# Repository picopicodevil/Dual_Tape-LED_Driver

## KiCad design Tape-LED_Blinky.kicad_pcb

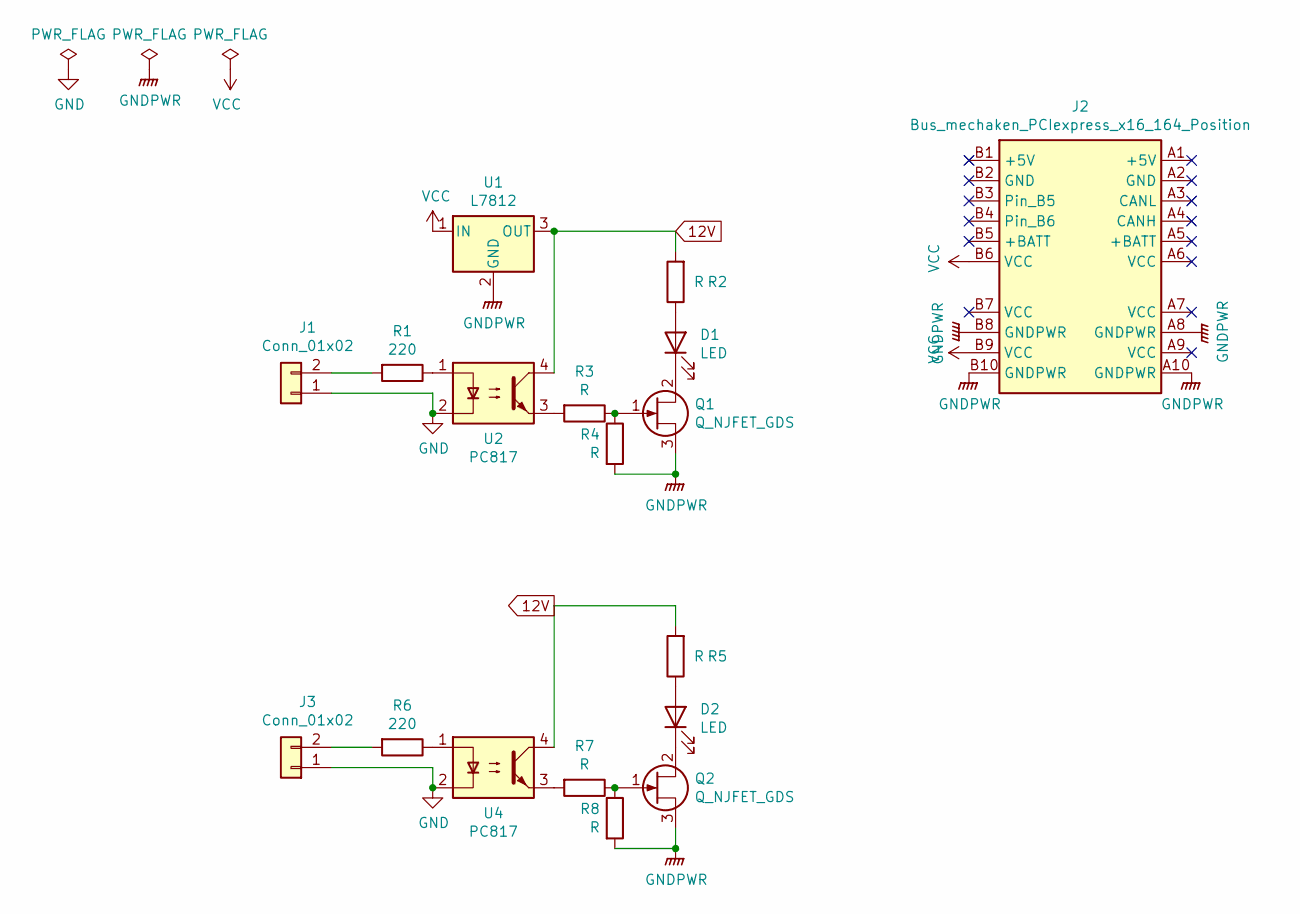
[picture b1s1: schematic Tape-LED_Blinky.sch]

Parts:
D1, D2: LED; PinHeader_1x02_P2.54mm_Vertical
J1, J3: Conn_01x02; PinHeader_1x02_P2.54mm_Vertical
J2: Bus_mechaken_PCIexpress_x16_164_Position; BUS_mechaken_PCIexpress_x16
Q1, Q2: Q_NJFET_GDS; TO-220-3_Vertical
R1, R6: 220; R_Axial_DIN0207_L6.3mm_D2.5mm_P10.16mm_Horizontal
R2, R3, R4, R5, R7, R8: R; R_Axial_DIN0207_L6.3mm_D2.5mm_P10.16mm_Horizontal
U1: L7812; TO-220-3_Vertical
U2, U4: PC817; DIP-4_W7.62mm

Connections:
12V: R2.2, R5.2, U1.3 (OUT), U2.4, U4.4
GND: J1.1, J3.1, U2.2, U4.2
GNDPWR: J2.A8 (GNDPWR), J2.A10 (GNDPWR), J2.B8 (GNDPWR), J2.B10 (GNDPWR), Q1.3 (S), Q2.3 (S), R4.2, R8.2, U1.2 (GND)
unnamed: D1.1 (K), Q1.2 (D)
unnamed: D1.2 (A), R2.1
unnamed: D2.1 (K), Q2.2 (D)
unnamed: D2.2 (A), R5.1
unnamed: J1.2, R1.2
unnamed: J3.2, R6.2
unnamed: Q1.1 (G), R3.1, R4.1
unnamed: Q2.1 (G), R7.1, R8.1
unnamed: R1.1, U2.1
unnamed: R3.2, U2.3
unnamed: R6.1, U4.1
unnamed: R7.2, U4.3
VCC: J2.B6 (VCC), J2.B9 (VCC), U1.1 (IN)

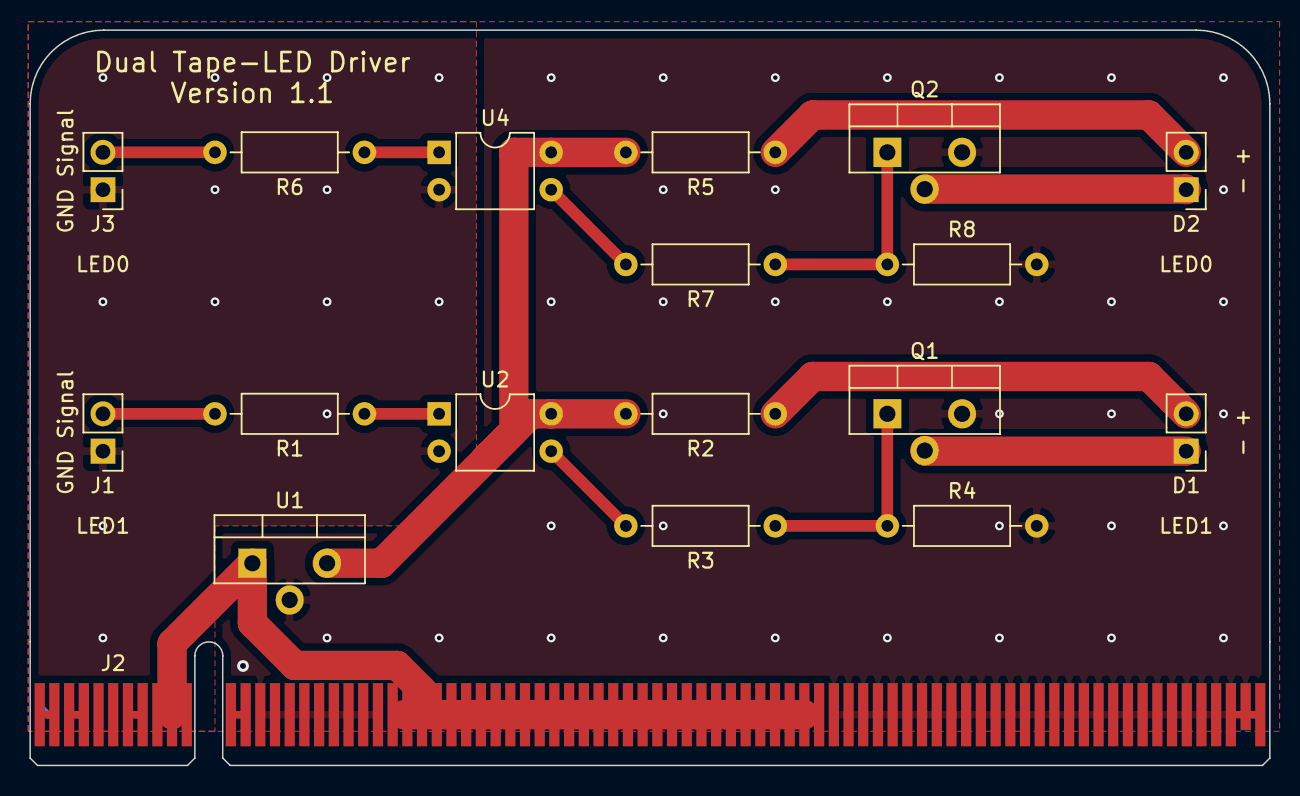
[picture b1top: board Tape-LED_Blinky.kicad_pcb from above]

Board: 2 copper layers, 84.3 x 50.0 mm, 18 parts (0 on the bottom side), 16 nets.

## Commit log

2020-02-02 Prototype-1.0
2020-02-02 create
2020-02-17 clean
2021-09-21 Add: .gitignore
2021-09-21 Remove: バックアップファイルを削除
2021-09-21 Remove: 発注用ファイルの削除
2021-09-21 Update: リポジトリのリンクの追加
2021-09-21 Update: バージョン表記の変更
2021-09-21 Update: 不確定だったR1, R6の抵抗値を決定
2021-09-24 Create LICENSE
2021-09-25 Update: フットプリントでも設定した抵抗値を反映
